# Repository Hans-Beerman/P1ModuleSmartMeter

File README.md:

**P1-module smart meter**

The P1-module is a small module, based on a Wemos D1 Mini (with an ESP8266) to collect information from the P1 port of a (Dutch) smart meter.

This module can be used for smart meters running DSMR Version 2.2 or higher.

For smart meters with DSMR V2.2 a jumper must be placed and the PCB must be powered by a 5V USB power supply. For more information, see the README.md in the KiCad directory of this repository

**Software for the P1-module**

The information collected from the smart meter is sent to a mqtt server of your own choice. The details about this server must be set in the .passwd.h file in the include directory of the PlatformIO project. This file must be added by yourself and should contain the following:

_/\* \*\*\*\*\*\*\*\*\*\*\*\*\*\*\*\*\*\*\*\*\*\*\*\*\*\*\*\*\*\*\*\*\*\*\*\*\*\*\*\*\*\*\*\*\*\*\*\*\*\*\*\*\*\*\*\*\*\*\*\*\*\*\*\*\*\*\*\*\*\*\*_

_PLEASE READ THIS FIRST_

_Add a file to the include directory of this project with the_

_following name:_

_.passwd.h_

_The content of this file should be:_

_#pragma once_

_// WiFi credentials_

_#define WIFI\_NETWORK &quot;YOUR\_WIFI\_NETWORK\_NAME&quot;_

_#define WIFI\_PASSWD &quot;YOUR\_WIFI\_NETWORK\_PASSWORD&quot;_

_#define FALLBACK\_WIFI\_NETWORK &quot;Dummy&quot; // or chose any other name you like_

_#define FALLBACK\_WIFI\_PASSWD &quot;12345678&quot; // or take another password_

_// mqtt server_

_#define MY\_MQTT\_HOST &quot;your\_mqtt\_host e.g. 10.10.10.10&quot;_

_#define MY\_MQTT\_PORT &quot;1883&quot;_

_#define MY\_MQTT\_USERNAME &quot;your\_mqtt\_server\_username&quot;_

_#define MY\_MQTT\_PASSWORD &quot;your\_mqtt\_server.password&quot;_

_// OTA credentials_

_#define OTA\_PASSWORD &quot;MyPassW00rd&quot; // must be the same in platformio.ini_

_Also check in the platformio.ini file the upload\_port set._

_In the current file this port is set for a serial connection to a_

_Linux Ubuntu PC for a Windows PC running Visual Studio Code with_

_PlatformIO you should use something like:_

_upload\_port = COM3_

_Or any other comport number which is used for the serial connection_

_For further information see the README.md in the repository on GitHub_

_\*\*\*\*\*\*\*\*\*\*\*\*\*\*\*\*\*\*\*\*\*\*\*\*\*\*\*\*\*\*\*\*\*\*\*\*\*\*\*\*\*\*\*\*\*\*\*\*\*\*\*\*\*\*\*\*\*\*\*\*\*\*\*\*\*\*\*\*\*\*\* \*/_

**WiFi network settings**

Default the P1-module uses the WiFi credentials as set in the .passw.h file, because in main.cpp the following #define is set:

_#define USE\_DEFAULT\_WIFI\_SETTINGS true_

If this #define is set to false:

_#define USE\_DEFAULT\_WIFI\_SETTINGS false_

In that case, if the P1-module is not able to connect to a WiFi network, the P1-module will set up a WiFi Access Point (AP) with the FALLBACK WiFi credentials as set in the .passwd.h file. Also a webserver (with IP address: 192.168.4.1) will be started.

If you connect, e.g. with a phone, a tablet or a PC to this AP, you will be able to select and configure a WiFi network and the mqtt server information, with the help of a web browser. The information set will be stored in eeprom.

**Overview of repository**

This repository has the following subdirs:

- **KiCad\_files:**

The design of the PCB used for the Node/Controller.

- **PlatformIO\_Files:**

The source code for the P1-module. For the development of this software PlatformIO is used, an Extension on Visual Studio Code.

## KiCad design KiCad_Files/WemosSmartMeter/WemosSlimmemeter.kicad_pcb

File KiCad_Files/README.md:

**P1-port smart meter module**

The following components are only needed if the smart meter uses DSMR version 2.2. For higher versions these components are not needed:

J3 USB connector

D1 Shottky diode

D2 Shottky diode, this diode must be replaced by a straight wire for higher DSMR versions.

J2 Jumper

In DSMR2.2 the USB connector is used to provide 5V, to be delivered by a 5V USB Power supply

For DSMR2.2 a jumper must be placed on J2, because the serial connection to the DSMR2.2 meter uses different settings. E.g. a baudrate of 9600 baud in DSMR2.2, while in highet DSMR versions the baudrate is 115200 baud.

**List of components used:**

J1 Header + cable with RJ12 connector, RJ12 naar 6 Pins Dupont-Jumper Adapter - P1 Kabel Compatible {e.g. [https://www.tinytronics.nl/shop/nl/kabels/adapters/rj12-naar-6-pins-dupont-jumper-adapter](https://www.tinytronics.nl/shop/nl/kabels/adapters/rj12-naar-6-pins-dupont-jumper-adapter))

J2 2-pole header (e.g. [https://www.tinytronics.nl/shop/nl/connectoren/pin-header/40-pins-header-male](https://www.tinytronics.nl/shop/nl/connectoren/pin-header/40-pins-header-male))

J3 USB-aansluitstekker printmontage Stekker, recht Typ A USB-stekker type A 774842 TRU COMPONENTS (e.g. [https://www.conrad.nl/p/usb-aansluitstekker-printmontage-stekker-recht-typ-a-usb-stekker-type-a-774842-tru-components-inhoud-1-stuks-1567162?searchTerm=USB-aansluitstekker%20printmontage%20Stekker&amp;searchType=suggest&amp;searchSuggest=product](https://www.conrad.nl/p/usb-aansluitstekker-printmontage-stekker-recht-typ-a-usb-stekker-type-a-774842-tru-components-inhoud-1-stuks-1567162?searchTerm=USB-aansluitstekker%20printmontage%20Stekker&amp;searchType=suggest&amp;searchSuggest=product))

U1 WeMos D1 Mini, Wemos D1 Mini V3 - ESP8266 - CH340 (e.g. [https://www.tinytronics.nl/shop/nl/arduino/wemos/wemos-d1-mini-v2-esp8266-12f-ch340](https://www.tinytronics.nl/shop/nl/arduino/wemos/wemos-d1-mini-v2-esp8266-12f-ch340))

Q1 BC546 (e.g. [https://www.tinytronics.nl/shop/nl/componenten/transistor-fet/npn-transistor-bc547](https://www.tinytronics.nl/shop/nl/componenten/transistor-fet/npn-transistor-bc547))

D1, D2 1N5819 (e.g. [https://www.conrad.nl/p/stmicroelectronics-skottky-diode-gelijkrichter-1n5819-do-41-40-v-enkelvoudig-155460](https://www.conrad.nl/p/stmicroelectronics-skottky-diode-gelijkrichter-1n5819-do-41-40-v-enkelvoudig-155460))

R1, R2 Resistor 1k (e.g. [https://www.conrad.nl/p/yageo-mf0207fte52-1k-metaalfilmweerstand-1-k-axiaal-bedraad-0207-06-w-1-1-stuks-1417606](https://www.conrad.nl/p/yageo-mf0207fte52-1k-metaalfilmweerstand-1-k-axiaal-bedraad-0207-06-w-1-1-stuks-1417606))

R3 Resistor 3k3 (e.g. [https://www.conrad.nl/p/yageo-mf0207fte52-3k3-metaalfilmweerstand-33-k-axiaal-bedraad-0207-06-w-1-1-stuks-1417733](https://www.conrad.nl/p/yageo-mf0207fte52-3k3-metaalfilmweerstand-33-k-axiaal-bedraad-0207-06-w-1-1-stuks-1417733))

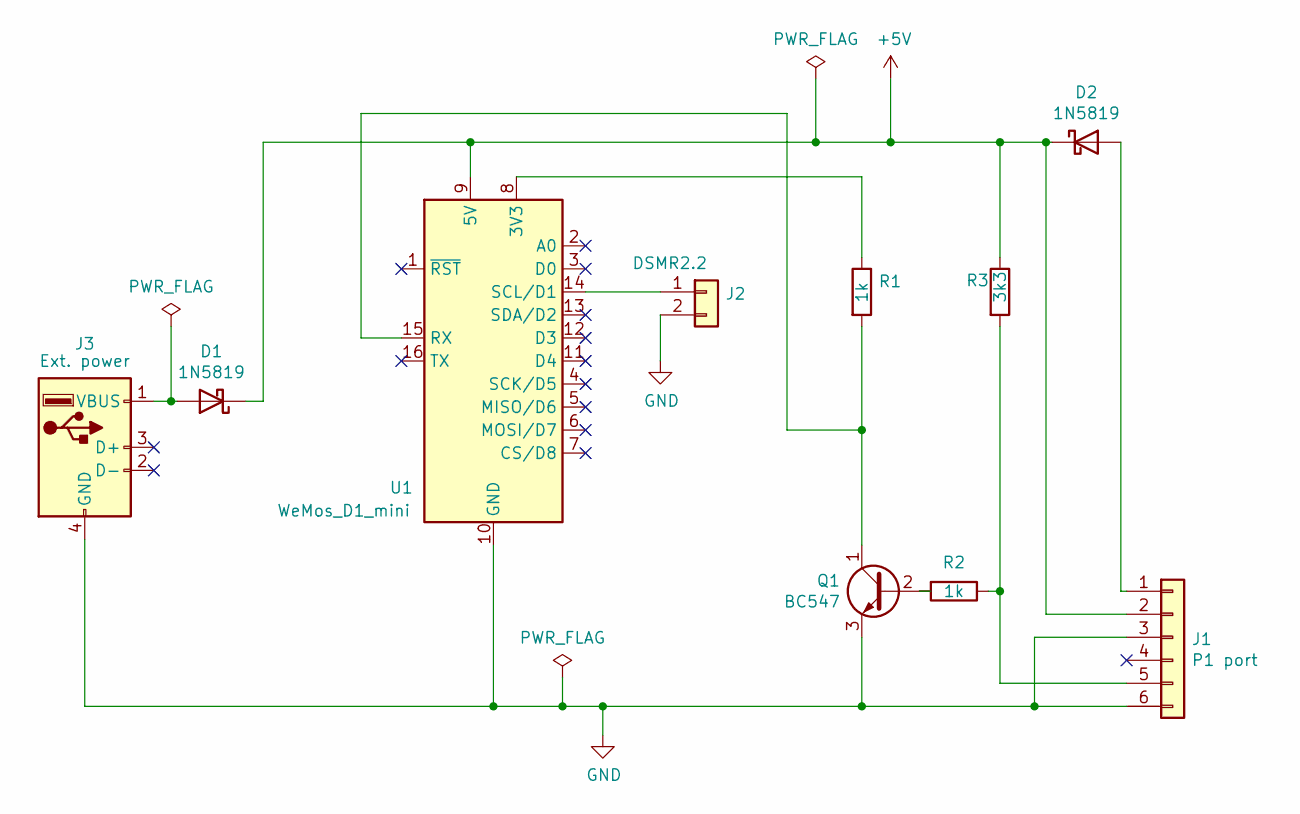
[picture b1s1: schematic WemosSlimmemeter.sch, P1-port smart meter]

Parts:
D1, D2: 1N5819; D_DO-41_SOD81_P10.16mm_Horizontal
J1: P1 port; PinHeader_1x06_P2.54mm_Horizontal
J2: DSMR2.2; PinHeader_1x02_P2.54mm_Vertical
J3: Ext. power; USB_A_Vertical
Q1: BC547; TO-92_Inline
R1, R2: 1k; R_Axial_DIN0207_L6.3mm_D2.5mm_P7.62mm_Horizontal
R3: 3k3; R_Axial_DIN0207_L6.3mm_D2.5mm_P7.62mm_Horizontal
U1: WeMos_D1_mini; WEMOS_D1_mini_light

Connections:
+5V: D1.1 (K), D2.1 (K), J1.2, R3.1, U1.9 (5V)
GND: J1.3, J1.6, J2.2, J3.4 (GND), Q1.3 (E), U1.10 (GND)
unnamed: D1.2 (A), J3.1 (VBUS)
unnamed: D2.2 (A), J1.1
unnamed: J1.5, R2.1, R3.2
unnamed: J2.1, U1.14 (SCL/D1)
unnamed: Q1.1 (C), R1.2, U1.15 (RX)
unnamed: Q1.2 (B), R2.2
unnamed: R1.1, U1.8 (3V3)

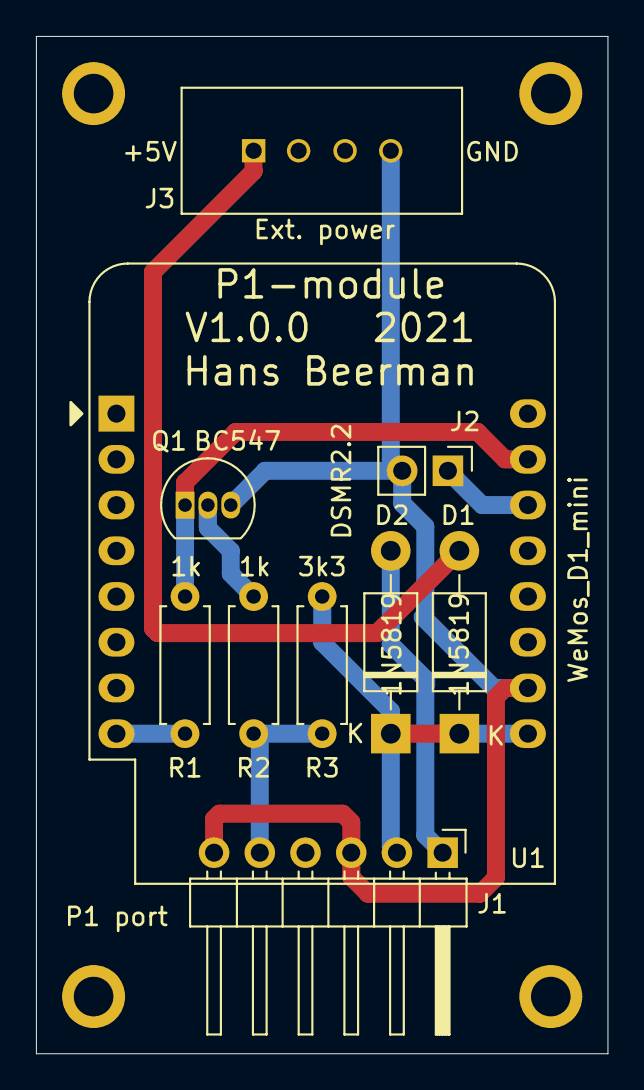
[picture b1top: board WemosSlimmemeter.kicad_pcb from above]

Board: 2 copper layers, 31.8 x 56.5 mm, 10 parts (0 on the bottom side), 9 nets.

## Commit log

2021-02-23 Version 1.0.0 first release
2021-02-23 Corrected a small typo in the README.md
2021-08-19 V1.0.0.0 corrected some typo's
2022-03-22 V1.0.0.1 Enlarged telegram buffer
2025-05-15 Commit 20250515 96:22:00
